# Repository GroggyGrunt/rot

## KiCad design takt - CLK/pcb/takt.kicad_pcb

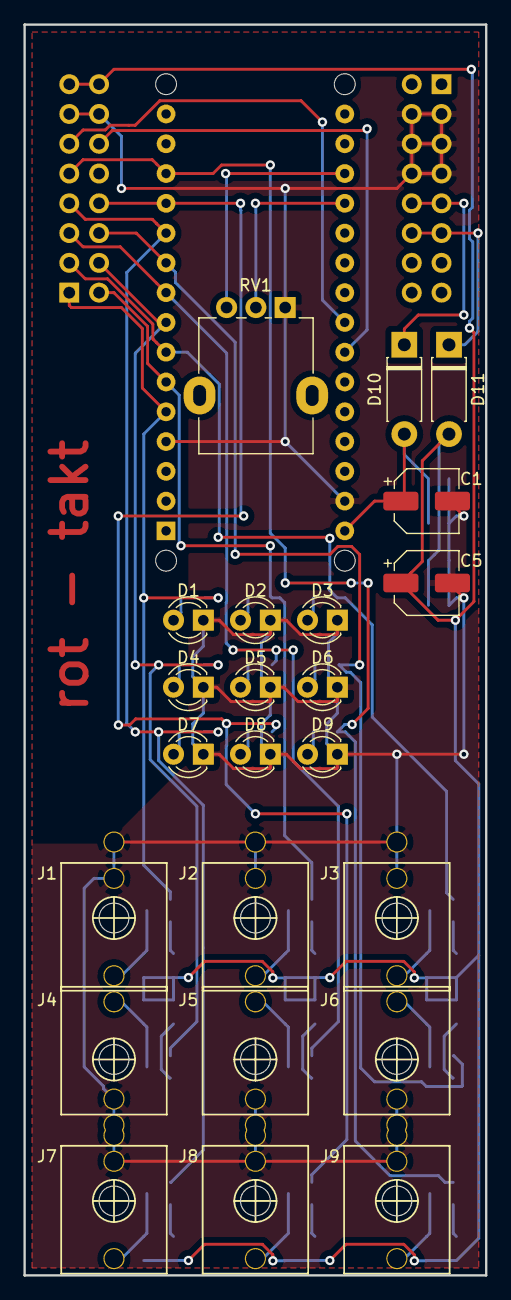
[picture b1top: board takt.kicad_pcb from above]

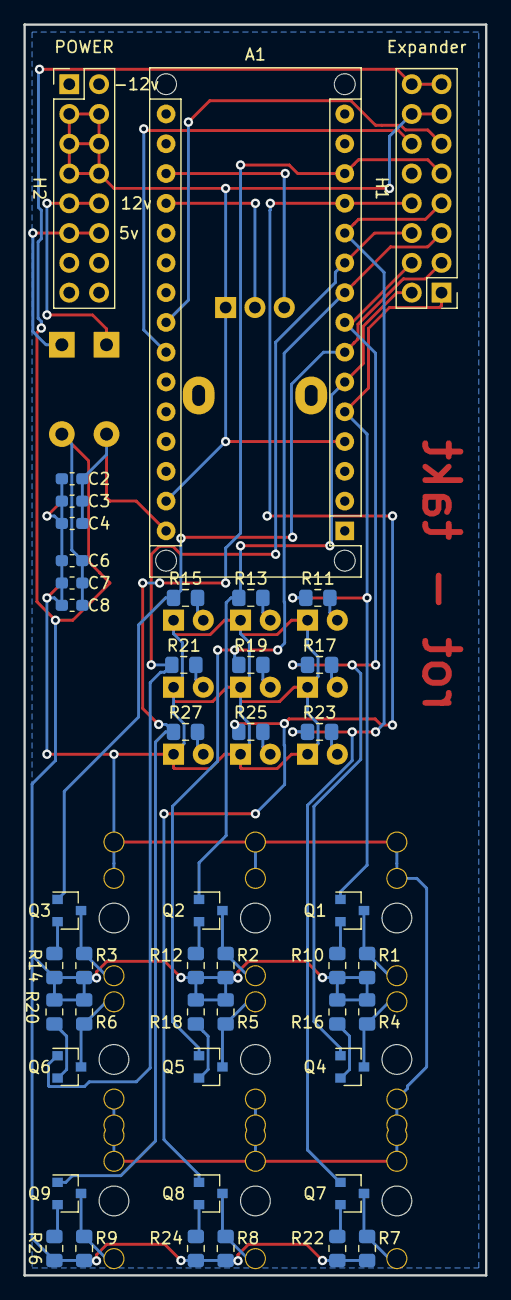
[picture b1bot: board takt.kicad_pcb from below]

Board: 2 copper layers, 39.4 x 106.7 mm, 68 parts (45 on the bottom side), 45 nets.

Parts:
A1: Arduino_Nano_v3.x; Arduino_Nano_WithMountingHoles
C1, C5: 470n; CP_Elec_5x5.3
C2, C3, C4, C6, C7, C8: 22n; C_0603_1608Metric_Pad1.05x0.95mm_HandSolder
D1, D2, D3, D4, D5, D6, D7, D8, D9: LED; LED_D3.0mm_FlatTop
D10, D11: 1N4006; D_DO-41_SOD81_P7.62mm_Horizontal
H1: Expander; PinHeader_2x08_P2.54mm_Vertical
H2: PIN_HEADER_2x8; PinHeader_2x08_P2.54mm_Vertical
J1, J2, J3, J4, J5, J6, J7, J8, J9: PJ301M-12
Q1, Q2, Q3, Q4, Q5, Q6, Q7, Q8, Q9: 2N3904; SOT-23
R1, R2, R3, R4, R5, R6, R7, R8, R9: 6.8k; R_0805_2012Metric_Pad1.15x1.40mm_HandSolder
R10, R12, R14, R16, R18, R20, R22, R24, R26: 2.2k; R_0805_2012Metric_Pad1.15x1.40mm_HandSolder
R11, R13, R15, R17, R19, R21, R23, R25, R27: 200; R_0805_2012Metric_Pad1.15x1.40mm_HandSolder
RV1: R_POT_US; Potentiometer_Alpha_RD901F-40-00D_Single_Vertical

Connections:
5V: C5.1, C6.1, C7.1, C8.1, D11.2, H1.15, H1.16, R1.1, R2.1, R3.1, R4.1, R5.1, R6.1, R7.1, R8.1, R9.1, R10.1, R12.1, R14.1, R16.1, R18.1, R20.1, R22.1, R24.1, R26.1
12V: A1.30, C1.1, C2.1, C3.1, C4.1, D10.2
GND: A1.4, A1.29, C1.2, C2.2, C3.2, C4.2, C5.2, C6.2, C7.2, C8.2, D1.1, D2.1, D3.1, D4.1, D5.1, D6.1, D7.1, D8.1, D9.1, H1.13, H1.14, H2.3, H2.4, H2.5, H2.6, H2.7, H2.8, J1.1, J1.2, J2.1, J2.2, J3.1, J3.2, J4.1, J4.2, J5.1, J5.2, J6.1, J6.2, J7.1, J7.2, J8.1, J8.2, J9.1, J9.2, RV1.1
unnamed: A1.18, RV1.3
unnamed: A1.19, RV1.2
unnamed: D1.2, R11.2
unnamed: D2.2, R13.2
unnamed: D3.2, R15.2
unnamed: D4.2, R17.2
unnamed: D5.2, R19.2
unnamed: D6.2, R21.2
unnamed: D7.2, R23.2
unnamed: D8.2, R25.2
unnamed: D9.2, R27.2
unnamed: D10.1, H2.9, H2.10
unnamed: D11.1, H2.11, H2.12
unnamed: J1.3, Q1.3, R1.2
unnamed: J2.3, Q2.3, R2.2
unnamed: J3.3, Q3.3, R3.2
unnamed: J4.3, Q4.3, R4.2
unnamed: J5.3, Q5.3, R5.2
unnamed: J6.3, Q6.3, R6.2
unnamed: J7.3, Q7.3, R7.2
unnamed: J8.3, Q8.3, R8.2
unnamed: J9.3, Q9.3, R9.2
unnamed: Q1.2, R10.2
unnamed: Q2.2, R12.2
unnamed: Q3.2, R14.2
unnamed: Q4.2, R16.2
unnamed: Q5.2, R18.2
unnamed: Q6.2, R20.2
unnamed: Q7.2, R22.2
unnamed: Q8.2, R24.2
unnamed: Q9.2, R26.2
SDA: A1.23, H1.11
SDC: A1.24, H1.12
Tr1: A1.5, H1.1, Q1.1, R11.1
Tr2: A1.6, H1.2, Q2.1, R13.1
Tr3: A1.7, H1.3, Q3.1, R15.1
Tr4: A1.8, H1.4, Q4.1, R17.1
Tr5: A1.9, H1.5, Q5.1, R19.1
Tr6: A1.10, H1.6, Q6.1, R21.1
Tr7: A1.11, H1.7, Q7.1, R23.1
Tr8: A1.12, H1.8, Q8.1, R25.1
Tr9: A1.13, H1.9, Q9.1, R27.1

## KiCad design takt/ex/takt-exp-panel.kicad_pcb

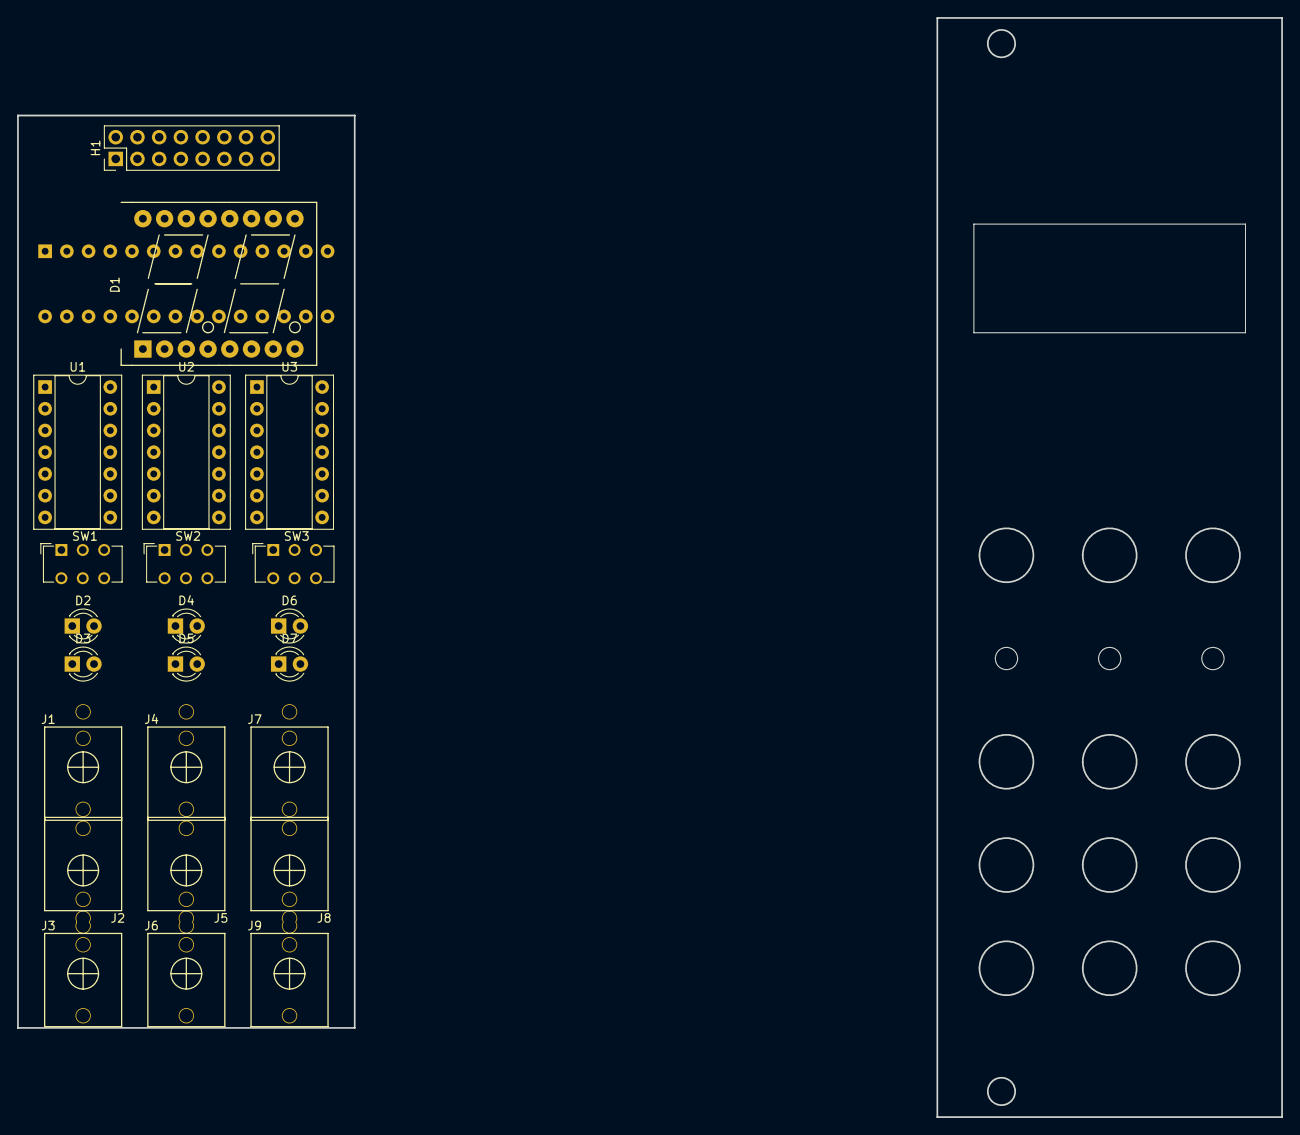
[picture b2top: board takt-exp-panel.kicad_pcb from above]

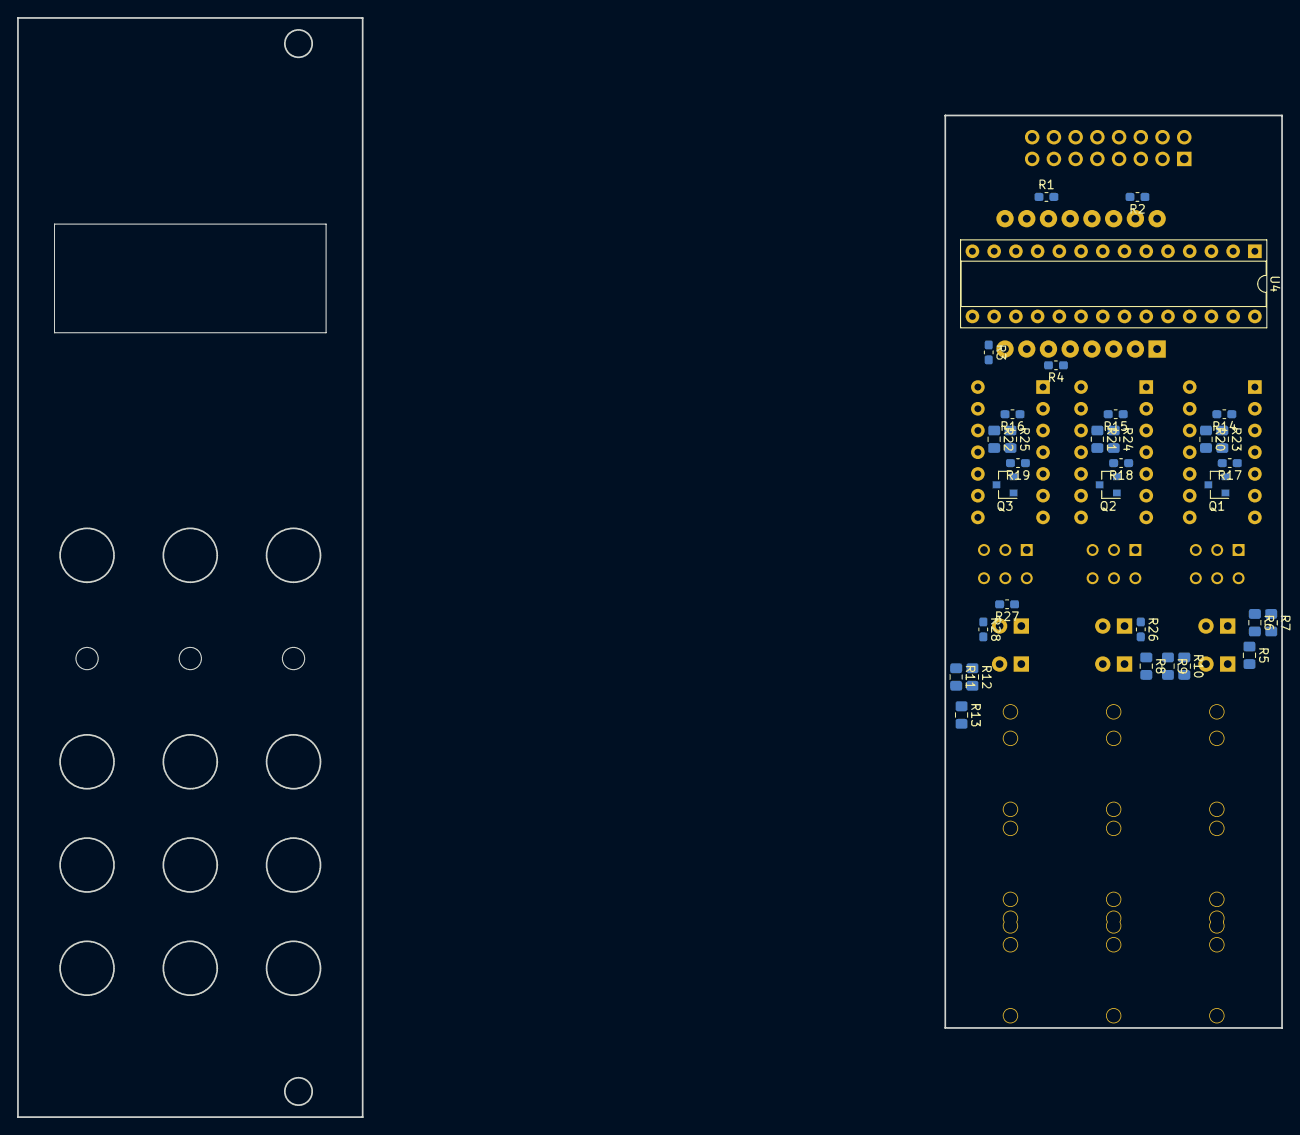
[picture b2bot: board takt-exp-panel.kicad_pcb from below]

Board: 2 copper layers, 39.4 x 106.7 mm, 55 parts (32 on the bottom side), 64 nets, no tracks yet.

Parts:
D1: CC56-12CGKWA; AFF_2x7SEG-DIGIT_10mm
D2, D3, D4, D5, D6, D7: LED; LED_D3.0mm_FlatTop
H1: Expander; PinHeader_2x08_P2.54mm_Vertical
J1, J2, J3, J4, J5, J6, J7, J8, J9: PJ301M-12
Q1, Q2, Q3: 2N3904; SOT-23
R1, R2, R3, R4, R26, R27, R28: 200; R_0603_1608Metric_Pad1.05x0.95mm_HandSolder
R5, R6, R7, R8, R9, R10, R11, R12, R13: 51; R_0805_2012Metric_Pad1.15x1.40mm_HandSolder
R14, R15, R16: 6.8k; R_0603_1608Metric_Pad1.05x0.95mm_HandSolder
R17, R18, R19: 2.2k; R_0603_1608Metric_Pad1.05x0.95mm_HandSolder
R20, R21, R22: 10m; R_0805_2012Metric_Pad1.15x1.40mm_HandSolder
R23, R24, R25: 1k; R_0805_2012Metric_Pad1.15x1.40mm_HandSolder
SW1, SW2, SW3: SW_SP3T; SW_CuK_JS202011CQN_DPDT_Straight
U1, U2, U3: TL074; DIP-14_W7.62mm_Socket
U4: ATmega328P-PU; DIP-28_W7.62mm_Socket

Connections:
5V: H1.15, H1.16, R14.1, R15.1, R16.1, R17.1, R18.1, R19.1, U1.4, U2.4, U3.4, U4.7, U4.20
C1: R1.1, U4.11
C2: R2.1, U4.6
C3: R3.1, U4.5
C4: R4.1, U4.4
GND: D5.1, D6.1, D7.1, H1.13, H1.14, J1.1, J2.1, J3.1, J4.1, J5.1, J6.1, J7.1, J8.1, J9.1, R20.2, R21.2, R22.2, R23.2, R24.2, R25.2, U1.11, U2.11, U3.11, U4.8, U4.22
La: D1.11, U4.12
Lb: D1.7, U4.13
Lc: D1.4, U4.14
Ld: D1.2, U4.15
Le: D1.1, U4.16
Lf: D1.10, U4.17
Lg: D1.5, U4.18
unnamed: D1.6, R4.2
unnamed: D1.8, R3.2
unnamed: D1.9, R2.2
unnamed: D1.12, R1.2
unnamed: D2.1, R23.1, U1.2
unnamed: D2.2, U1.1
unnamed: D3.1, R24.1, U2.2
unnamed: D3.2, U2.1
unnamed: D4.1, R25.1, U3.2
unnamed: D4.2, U3.1
unnamed: D5.2, R26.2
unnamed: D6.2, R27.2
unnamed: D7.2, R28.2
unnamed: J1.3, R5.2
unnamed: J2.3, R6.2
unnamed: J3.3, R7.2
unnamed: J4.3, R8.2
unnamed: J5.3, R9.2
unnamed: J6.3, R10.2
unnamed: J7.3, R11.2
unnamed: J8.3, R12.2
unnamed: J9.3, R13.2
unnamed: Q1.2, R17.2
unnamed: Q1.3, R14.2, R20.1, U1.3, U1.5, U1.10, U1.12
unnamed: Q2.2, R18.2
unnamed: Q2.3, R15.2, R21.1, U2.3, U2.5, U2.10, U2.12
unnamed: Q3.2, R19.2
unnamed: Q3.3, R16.2, R22.1, U3.3, U3.5, U3.10, U3.12
unnamed: R5.1, U1.6, U1.7
unnamed: R6.1, U1.8, U1.9
unnamed: R7.1, U1.13, U1.14
unnamed: R8.1, U2.6, U2.7
unnamed: R9.1, U2.8, U2.9
unnamed: R10.1, U2.13, U2.14
unnamed: R11.1, U3.6, U3.7
unnamed: R12.1, U3.8, U3.9
unnamed: R13.1, U3.13, U3.14
SDA: H1.11, U4.27
SDC: H1.12, U4.28
Tr1: H1.1, SW1.1
Tr2: H1.2, SW1.2
Tr3: H1.3, SW1.4
Tr4: H1.4, SW2.1
Tr5: H1.5, SW2.2
Tr6: H1.6, SW2.4
Tr7: H1.7, SW3.1
Tr8: H1.8, SW3.2
Tr9: H1.9, SW3.4
sw1: Q1.1, R26.1, SW1.3
sw2: Q2.1, R27.1, SW2.3
sw3: Q3.1, R28.1, SW3.3
